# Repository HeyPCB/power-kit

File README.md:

# HeyPCB Power Kit

Six small power and charging boards, each a complete KiCad 10 project with Gerbers, BOM and a CPL fitted to JLCPCB's own footprints.

| Board | What it does | Size | DRC errors / unconnected / parity |
|---|---|---|---|
| [Dual Rail](boards/dual-rail/) | 6-15 V to 5 V / 3 A + 3.3 V / 2 A | 50 x 36 mm, 4 layers | 0 / 0 / 0 |
| [PD Trigger](boards/pd-trigger/) | USB-C PD sink, DIP-selected 5-20 V | 28 x 40 mm, 2 layers | 0 / 0 / 0 |
| [1S Boost](boards/boost-1s/) | One lithium cell to 5.1 V | 28 x 30 mm, 2 layers | 0 / 0 / 0 |
| [Power Mux](boards/power-mux/) | USB-C first, 1S cell as backup | 28 x 32 mm, 2 layers | 0 / 0 / 0 |
| [USB eFuse](boards/usb-efuse/) | 5 V inline protection | 26 x 30 mm, 2 layers | 0 / 0 / 0 |
| [USB-C Power Meter](boards/usb-c-meter/) | Inline power monitor, Qwiic | 32 x 24 mm, 2 layers | 0 / 0 / 0 |

<p align="center">     </p>

**Not fabricated, assembled or powered.** Every number in a board's README is measured by KiCad 10 on the files in its folder (`report.json`). Parts are LCSC-numbered and were in JLCPCB's stock on the date each README gives.

Each board folder holds `kicad/` (project), `fab/` (Gerbers zip, BOM, CPL, STEP, schematic PDF), `media/` (renders and a design-process video) and `board.json` (the brief it was built from).

Designed with the HeyPCB method on KiCad 10 by heypcb-kicad's headless pipeline with Freerouting 2.4.1.

## Licence

CERN-OHL-S-2.0, © 2026 heypcb.ai. See [LICENSE](LICENSE).

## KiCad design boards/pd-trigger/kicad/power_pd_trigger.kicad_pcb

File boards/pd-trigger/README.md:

# PD Trigger

A USB-C Power Delivery trigger: any PD charger in, a fixed 5, 9, 12, 15 or 20 V at 3 A out on a screw terminal, picked with a DIP switch.

| Layers | Size | Parts | Nets | Connections routed | Vias | ERC errors | DRC errors / unconnected / parity |
|---|---|---|---|---|---|---|---|
| 2 | 28 x 40 mm | 17 | 15 | 47 -> 0 open | 35 | 0 | 0 / 0 / 0 |

**Not fabricated, assembled or powered.** Every number on this page is measured by KiCad 10 on the files in this folder; the full measurements are in [`report.json`](report.json).

| | |
|---|---|
| KiCad project | [`kicad/`](kicad/) |
| Gerbers, BOM, CPL, STEP, schematic PDF | [`fab/`](fab/) |
| Renders | [top](media/top.png), [bottom](media/bottom.png) |
| Design process, every step as KiCad rendered it | [`media/design-process.mp4`](media/design-process.mp4) |

Plug a USB-C PD charger in and get one fixed voltage out, for powering a bench project, a strip of LEDs or a 12 V tool from a laptop charger. A Hynetek HUSB238 negotiates the contract and only then turns on a P-FET onto the output terminal, so nothing downstream sees a voltage it did not ask for. A 4-way DIP switch picks 5, 9, 12 or 15 V; all switches off asks for 20 V. Designed with the HeyPCB method on KiCad 10, by heypcb-kicad's headless pipeline with Freerouting 2.4.1, from the brief in `board.json`.

## Specs

- **Input:** USB-C receptacle (CC1 and CC2 to the HUSB238; D+ and D- wired for chargers that look at them).
- **Voltage select:** a 4-way DIP switch puts one resistor on VSET (HUSB238 table 6): 0 = 5 V, 6.04k = 9 V, 10k = 12 V, 14k = 15 V, nothing = 20 V. Turn on one switch at most; the positions are labelled on both faces.
- **Current request:** ISET 22.6k = 3.0 A. Not 3.25 A (ISET open), because a standard 3 A charger cannot meet 3.25 A and the HUSB238 would fall back to a lower voltage.
- **Output switch:** DMP3013SFV P-FET (-30 V, 9.5 mOhm at VGS -10 V, about 0.09 W at 3 A) driven by the HUSB238's open-drain GATE through 10k, with a 10 V zener holding VGS inside its rating at 20 V.
- **Output:** 5 mm MaiXu MX126 2-pin screw terminal, SMBJ24A TVS across it, green LED when the output is on.
- **Current paths:** VBUS and the switched output are copper zones, not tracks.
- **Board:** 28 x 40 mm, 2 layers, 1.6 mm.

## Parts

Every line carries an LCSC part number. Stock is JLCPCB's assembly stock on 2026-10-18.

| Designators | Value | LCSC | MPN | JLCPCB tier | Stock |
|---|---|---|---|---|---|
| C1 | 1uF | C15849 | CL10A105KB8NNNC | Basic | 9,261,663 |
| C2 | 1uF | C28323 | CL21B105KBFNNNE | Basic | 2,337,702 |
| D1 | BZT52C10 | C173431 | BZT52C10 | Extended | 277,380 |
| D2 | SMBJ24A | C123819 | SMBJ24A | Extended | 59,843 |
| D3 | Green (OUT) | C12624 | KT-0603G | Extended | 500,718 |
| J1 | USB-C PD IN | C165948 | TYPE-C-31-M-12 | Extended | 362,231 |
| J2 | OUT | C5188434 | MX126-5.0-02P-GN01-Cu-S-A | Extended | 35,962 |
| Q1 | DMP3013SFV | C264098 | DMP3013SFV-7 | Extended | 3,984 |
| R1 | 6.04k | C25977 | 0603WAF6041T5E | Extended | 135,034 |
| R2,R5,R7 | 10k | C25804 | 0603WAF1002T5E | Basic | 39,990,901 |
| R3 | 14k | C22803 | 0603WAF1402T5E | Extended | 11,051 |
| R4 | 22.6k | C2999509 | FRC0603F2262TS | Extended | 92,673 |
| R6 | 100k | C25803 | 0603WAF1003T5E | Basic | 19,336,314 |
| SW1 | VSET 5/9/12/15 | C6331176 | 2.54-4P TPGT | Extended | 45,129 |
| U1 | HUSB238_002DD | C7471904 | HUSB238_002DD | Extended | 13,737 |

## Ordering

- PCB: upload `fab/power_pd_trigger_gerbers.zip`, 2 layers, 28 x 40 mm, 1.6 mm.
- Assembly: `fab/power_pd_trigger_bom.csv` and `fab/power_pd_trigger_cpl_jlc.csv`, top side.
- The CPL is fitted to each part's own JLCPCB footprint, pad by pad, and re-checked by laying each footprint where its row says: 17 of 17 rows fitted, worst pin-to-pad offset 0.21 mm.

## Notes

- The 3 A rating is the request the board makes; whether a charger gives 3 A at the chosen voltage is the charger's PDO list. Nothing here is measured at load: the board has not been built.
- The DMP3013SFV (C264098) had 3,984 in JLCPCB's stock when this was packaged, the lowest of the parts list. Check it before ordering.
- SDA and SCL are not connected; the HUSB238's I2C mode is not used.
- The USB-C receptacle (HRO TYPE-C-31-M-12) renders as a plain box: KiCad's library footprint names a 3D model that KiCad does not ship. The footprint and its pads are KiCad's own and are fitted to JLCPCB's land.

## How it was made

Designed with the HeyPCB method on KiCad 10, by heypcb-kicad's headless pipeline with Freerouting 2.4.1, from the brief in [`board.json`](board.json).

## Licence

CERN-OHL-S-2.0, © 2026 heypcb.ai. See the collection's LICENSE.

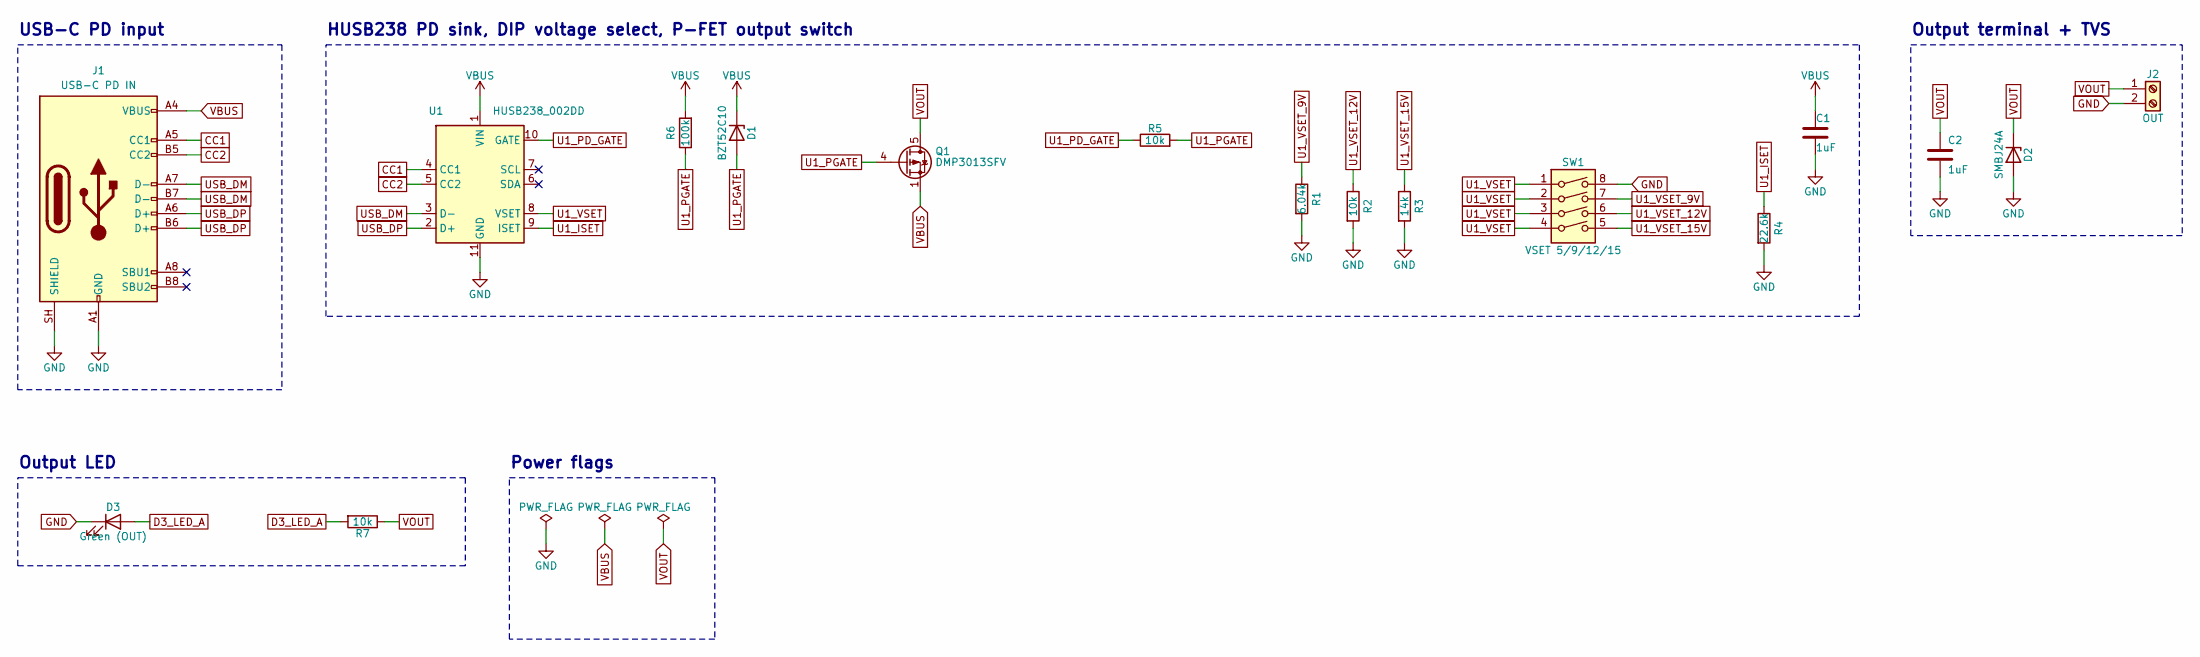
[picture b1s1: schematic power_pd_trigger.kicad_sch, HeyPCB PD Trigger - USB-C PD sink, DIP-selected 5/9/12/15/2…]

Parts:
C1: 1uF; C_0603_1608Metric; MPN CL10A105KB8NNNC; LCSC C15849
C2: 1uF; C_0805_2012Metric; MPN CL21B105KBFNNNE; LCSC C28323
D1: BZT52C10; D_SOD-123; MPN BZT52C10; LCSC C173431
D2: SMBJ24A; D_SMB; MPN SMBJ24A; LCSC C123819
D3: Green (OUT); LED_0603_1608Metric; MPN KT-0603G; LCSC C12624
J1: USB-C PD IN; USB_C_Receptacle_HRO_TYPE-C-31-M-12; MPN TYPE-C-31-M-12; LCSC C165948
J2: OUT; TerminalBlock_MaiXu_MX126-5.0-02P_1x02_P5.00mm; MPN MX126-5.0-02P-GN01-Cu-S-A; LCSC C5188434
Q1: DMP3013SFV; Diodes_PowerDI3333-8; MPN DMP3013SFV-7; LCSC C264098
R1: 6.04k; R_0603_1608Metric; MPN 0603WAF6041T5E; LCSC C25977
R2, R5, R7: 10k; R_0603_1608Metric; MPN 0603WAF1002T5E; LCSC C25804
R3: 14k; R_0603_1608Metric; MPN 0603WAF1402T5E; LCSC C22803
R4: 22.6k; R_0603_1608Metric; MPN FRC0603F2262TS; LCSC C2999509
R6: 100k; R_0603_1608Metric; MPN 0603WAF1003T5E; LCSC C25803
SW1: VSET 5/9/12/15; SW_DIP_SPSTx04_Slide_Omron_A6S-410x_W8.9mm_P2.54mm; MPN 2.54-4P TPGT; LCSC C6331176
U1: HUSB238_002DD; WDFN-10-1EP_3x3mm_P0.5mm_EP1.8x2.5mm; MPN HUSB238_002DD; LCSC C7471904

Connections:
CC1: J1.A5 (CC1), U1.4 (CC1)
CC2: J1.B5 (CC2), U1.5 (CC2)
D3_LED_A: D3.2 (A), R7.2
GND: C1.2, C2.2, D2.2 (A), D3.1 (K), J1.A1 (GND), J1.A12 (GND), J1.B1 (GND), J1.B12 (GND), J1.SH (SHIELD), J2.2, R1.2, R2.2, R3.2, R4.2, SW1.8, U1.11 (GND)
U1_ISET: R4.1, U1.9 (ISET)
U1_PD_GATE: R5.1, U1.10 (GATE)
U1_PGATE: D1.2 (A), Q1.4 (G), R5.2, R6.1
U1_VSET: SW1.1, SW1.2, SW1.3, SW1.4, U1.8 (VSET)
U1_VSET_9V: R1.1, SW1.7
U1_VSET_12V: R2.1, SW1.6
U1_VSET_15V: R3.1, SW1.5
USB_DM: J1.A7 (D-), J1.B7 (D-), U1.3 (D-)
USB_DP: J1.A6 (D+), J1.B6 (D+), U1.2 (D+)
VBUS: C1.1, D1.1 (K), J1.A4 (VBUS), J1.A9 (VBUS), J1.B4 (VBUS), J1.B9 (VBUS), Q1.1 (S), Q1.2 (S), Q1.3 (S), R6.2, U1.1 (VIN)
VOUT: C2.1, D2.1 (K), J2.1, Q1.5 (D), R7.1

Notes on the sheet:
USB-C PD input
HUSB238 PD sink, DIP voltage select, P-FET output switch
Output terminal + TVS
Output LED
Power flags

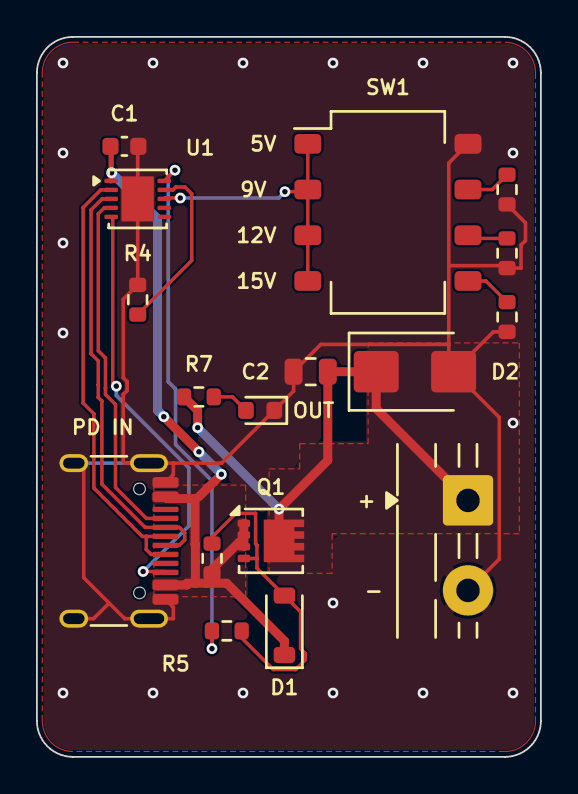
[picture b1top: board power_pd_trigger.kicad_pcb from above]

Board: 2 copper layers, 28.0 x 40.0 mm, 17 parts (0 on the bottom side), 15 nets.

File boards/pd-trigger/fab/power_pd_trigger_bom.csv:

"Reference","Value","Footprint","MPN","LCSC","Qty"
"C1","1uF","Capacitor_SMD:C_0603_1608Metric","CL10A105KB8NNNC","C15849","1"
"C2","1uF","Capacitor_SMD:C_0805_2012Metric","CL21B105KBFNNNE","C28323","1"
"D1","BZT52C10","Diode_SMD:D_SOD-123","BZT52C10","C173431","1"
"D2","SMBJ24A","Diode_SMD:D_SMB","SMBJ24A","C123819","1"
"D3","Green (OUT)","LED_SMD:LED_0603_1608Metric","KT-0603G","C12624","1"
"J1","USB-C PD IN","Connector_USB:USB_C_Receptacle_HRO_TYPE-C-31-M-12","TYPE-C-31-M-12","C165948","1"
"J2","OUT","TerminalBlock:TerminalBlock_MaiXu_MX126-5.0-02P_1x02_P5.00mm","MX126-5.0-02P-GN01-Cu-S-A","C5188434","1"
"Q1","DMP3013SFV","Package_SON:Diodes_PowerDI3333-8","DMP3013SFV-7","C264098","1"
"R1","6.04k","Resistor_SMD:R_0603_1608Metric","0603WAF6041T5E","C25977","1"
"R2,R5,R7","10k","Resistor_SMD:R_0603_1608Metric","0603WAF1002T5E","C25804","3"
"R3","14k","Resistor_SMD:R_0603_1608Metric","0603WAF1402T5E","C22803","1"
"R4","22.6k","Resistor_SMD:R_0603_1608Metric","FRC0603F2262TS","C2999509","1"
"R6","100k","Resistor_SMD:R_0603_1608Metric","0603WAF1003T5E","C25803","1"
"SW1","VSET 5/9/12/15","Button_Switch_SMD:SW_DIP_SPSTx04_Slide_Omron_A6S-410x_W8.9mm_P2.54mm","2.54-4P TPGT","C6331176","1"
"U1","HUSB238_002DD","Package_DFN_QFN:WDFN-10-1EP_3x3mm_P0.5mm_EP1.8x2.5mm","HUSB238_002DD","C7471904","1"

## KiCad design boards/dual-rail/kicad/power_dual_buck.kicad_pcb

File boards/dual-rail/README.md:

# Dual Rail

A dual-rail buck module: 6-15 V in, 5 V / 3 A and 3.3 V / 2 A out, reverse-polarity protected.

| Layers | Size | Parts | Nets | Connections routed | Vias | ERC errors | DRC errors / unconnected / parity |
|---|---|---|---|---|---|---|---|
| 4 | 50 x 36 mm | 34 | 14 | 57 -> 0 open | 70 | 0 | 0 / 0 / 0 |

**Not fabricated, assembled or powered.** Every number on this page is measured by KiCad 10 on the files in this folder; the full measurements are in [`report.json`](report.json).

| | |
|---|---|
| KiCad project | [`kicad/`](kicad/) |
| Gerbers, BOM, CPL, STEP, schematic PDF | [`fab/`](fab/) |
| Renders | [top](media/top.png), [bottom](media/bottom.png) |
| Design process, every step as KiCad rendered it | [`media/design-process.mp4`](media/design-process.mp4) |

A small power module for the bench and for projects that need both 5 V and 3.3 V from one 6-15 V supply (a 12 V adapter, a 3S pack). A TPS563201 synchronous buck makes 5 V and an AP63203 makes 3.3 V, both straight from the protected input, so neither rail's load heats the other's regulator. The input has a reverse-polarity P-FET and a TVS, every rail has an LED, and VIN, 5V, 3V3 and GND come out on a 2.54 mm header. Designed with the HeyPCB method on KiCad 10 (10.0.6), by heypcb-kicad's headless pipeline with Freerouting 2.4.1, from the brief in `board.json`.

## Specs

- **Input:** 6-15 V DC on a 5 mm MaiXu MX126 screw terminal, marked + and -. The input range stops at 15 V because the TPS563201 is rated to 17 V input (TI SLVSD90B).
- **Reverse polarity:** AO3401A P-FET in the + lead (drain on the terminal, source on the board). A BZT52C10 zener and a 100k resistor hold its gate-source voltage at about -10 V, inside its +-12 V rating, across the whole input range.
- **Transients:** SMAJ15A TVS on the protected input (15 V stand-off, 24.4 V clamp at 16.4 A). It is for transients, not for a sustained over-voltage. 2 x 22 uF / 25 V X5R input bulk.
- **5 V rail:** TPS563201 synchronous buck (TI, 3 A, 580 kHz), 4.7 uH Sunlord SWPA6045S inductor, 3 x 22 uF output. Feedback 82k / 15k: VFB 0.768 V gives 4.96 V.
- **3.3 V rail:** AP63203 fixed 3.3 V synchronous buck (Diodes, 2 A, 1.1 MHz), 4.7 uH Sunlord SWPA4030S inductor, 2 x 22 uF output.
- **Current paths:** the raw input, the protected input, both switch nodes, 5V and 3V3 are copper zones on F.Cu, not tracks. The input zones at each converter are stitched to an In2 VIN plane, and In1 is a solid GND plane.
- **Outputs:** VIN, 5V, 3V3 and GND on a 1x4 2.54 mm header, labelled on both faces; a green LED on each rail.
- **Board:** 50 x 36 mm, 4 layers (F.Cu / In1 GND / In2 VIN + routing / B.Cu), 1.6 mm, four M3 holes at the corners.

## Parts

Every line carries an LCSC part number. Stock is JLCPCB's assembly stock on 2026-10-18.

| Designators | Value | LCSC | MPN | JLCPCB tier | Stock |
|---|---|---|---|---|---|
| C1,C2 | 22uF | C12891 | CL31A226KAHNNNE | Basic | 490,725 |
| C3,C4,C7,C8,C9,C12,C13 | 22uF | C45783 | CL21A226MAQNNNE | Basic | 3,755,166 |
| C5,C6,C11 | 100nF | C14663 | CC0603KRX7R9BB104 | Basic | 31,787,100 |
| C10 | 10uF | C13585 | CL31A106KBHNNNE | Basic | 2,283,157 |
| D1 | BZT52C10 | C173431 | BZT52C10 | Extended | 277,380 |
| D2 | SMAJ15A | C908769 | SMAJ15A | Extended | 112,547 |
| D3 | Green (5V) | C12624 | KT-0603G | Extended | 500,718 |
| D4 | Green (3V3) | C12624 | KT-0603G | Extended | 500,718 |
| J1 | VIN 6-15V | C5188434 | MX126-5.0-02P-GN01-Cu-S-A | Extended | 35,962 |
| J2 | OUT | C2691448 | PZ254V-11-04P | Extended | 887,860 |
| L1 | 4.7uH | C78804 | SWPA6045S4R7MT | Extended | 30,574 |
| L2 | 4.7uH | C57269 | SWPA4030S4R7MT | Extended | 19,258 |
| Q1 | AO3401A | C15127 | AO3401A | Basic | 696,636 |
| R1,R4 | 100k | C25803 | 0603WAF1003T5E | Basic | 19,342,480 |
| R2 | 82k | C23254 | 0603WAF8202T5E | Basic | 1,210,269 |
| R3 | 15k | C22809 | 0603WAF1502T5E | Basic | 4,101,125 |
| R5 | 2.2k | C4190 | 0603WAF2201T5E | Basic | 6,541,747 |
| R6 | 1k | C21190 | 0603WAF1001T5E | Basic | 23,229,534 |
| U1 | TPS563201 | C116592 | TPS563201DDCR | Extended | 114,139 |
| U2 | AP63203WU-7 | C780769 | AP63203WU-7 | Extended | 3,515 |

## Ordering

- PCB: upload `fab/power_dual_buck_gerbers.zip`, 4 layers, 50 x 36 mm, 1.6 mm.
- Assembly: `fab/power_dual_buck_bom.csv` and `fab/power_dual_buck_cpl_jlc.csv`, top side.
- The CPL is fitted to each part's own JLCPCB footprint, pad by pad, and re-checked by laying each footprint where its row says: 28 of 30 rows fitted, worst pin-to-pad offset 0.28 mm.
- Not fitted (no JLCPCB footprint to fit to), rotation from KiCad's: L1, L2. Check these in JLCPCB's placement preview.

## Notes

- The output ratings (3 A, 2 A) are the converters' datasheet ratings. Nothing here measures temperature or ripple at load: the board has not been built.
- The AP63203WU-7 (C780769) has one LCSC listing; 3,515 in stock when this was packaged. The same part is on PD Brick, Spinner and Ice Core.
- L1 and L2 (Sunlord SWPA inductors) are not in EasyEDA's footprint library, so their CPL rotation is KiCad's and was not fitted. Both are symmetric two-pad parts with their pads along x in KiCad. Check them in JLCPCB's placement preview.

## How it was made

Designed with the HeyPCB method on KiCad 10, by heypcb-kicad's headless pipeline with Freerouting 2.4.1, from the brief in [`board.json`](board.json).

## Licence

CERN-OHL-S-2.0, © 2026 heypcb.ai. See the collection's LICENSE.

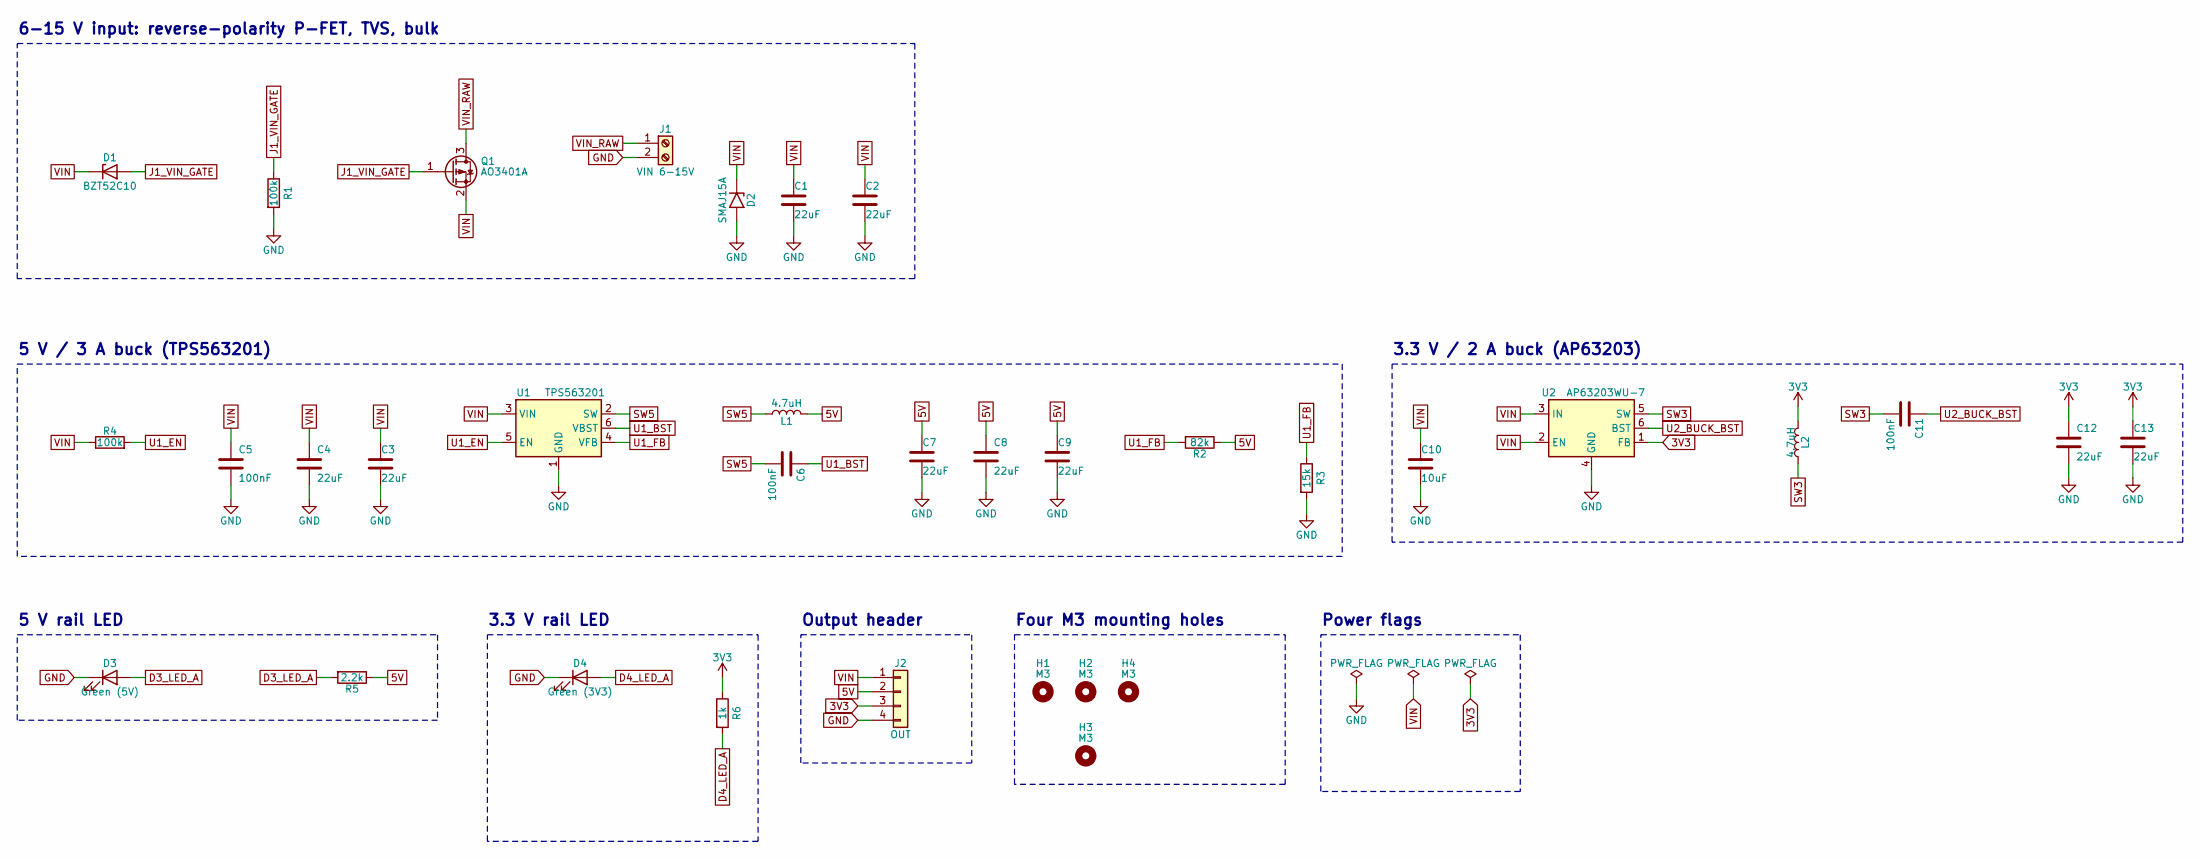
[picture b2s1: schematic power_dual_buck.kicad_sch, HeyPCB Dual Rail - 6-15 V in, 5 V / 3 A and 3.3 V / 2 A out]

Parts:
C1, C2: 22uF; C_1206_3216Metric; MPN CL31A226KAHNNNE; LCSC C12891
C3, C4, C7, C8, C9, C12, C13: 22uF; C_0805_2012Metric; MPN CL21A226MAQNNNE; LCSC C45783
C5, C6, C11: 100nF; C_0603_1608Metric; MPN CC0603KRX7R9BB104; LCSC C14663
C10: 10uF; C_1206_3216Metric; MPN CL31A106KBHNNNE; LCSC C13585
D1: BZT52C10; D_SOD-123; MPN BZT52C10; LCSC C173431
D2: SMAJ15A; D_SMA; MPN SMAJ15A; LCSC C908769
D3: Green (5V); LED_0603_1608Metric; MPN KT-0603G; LCSC C12624
D4: Green (3V3); LED_0603_1608Metric; MPN KT-0603G; LCSC C12624
H1, H2, H3, H4: M3; MountingHole_3.2mm_M3
J1: VIN 6-15V; TerminalBlock_MaiXu_MX126-5.0-02P_1x02_P5.00mm; MPN MX126-5.0-02P-GN01-Cu-S-A; LCSC C5188434
J2: OUT; PinHeader_1x04_P2.54mm_Vertical; MPN PZ254V-11-04P; LCSC C2691448
L1: 4.7uH; L_Sunlord_SWPA6045S; MPN SWPA6045S4R7MT; LCSC C78804
L2: 4.7uH; L_Sunlord_SWPA4030S; MPN SWPA4030S4R7MT; LCSC C57269
Q1: AO3401A; SOT-23; MPN AO3401A; LCSC C15127
R1, R4: 100k; R_0603_1608Metric; MPN 0603WAF1003T5E; LCSC C25803
R2: 82k; R_0603_1608Metric; MPN 0603WAF8202T5E; LCSC C23254
R3: 15k; R_0603_1608Metric; MPN 0603WAF1502T5E; LCSC C22809
R5: 2.2k; R_0603_1608Metric; MPN 0603WAF2201T5E; LCSC C4190
R6: 1k; R_0603_1608Metric; MPN 0603WAF1001T5E; LCSC C21190
U1: TPS563201; SOT-23-6; MPN TPS563201DDCR; LCSC C116592
U2: AP63203WU-7; TSOT-23-6; MPN AP63203WU-7; LCSC C780769

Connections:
3V3: C12.1, C13.1, J2.3, L2.2, R6.1, U2.1 (FB)
5V: C7.1, C8.1, C9.1, J2.2, L1.2, R2.1, R5.1
D3_LED_A: D3.2 (A), R5.2
D4_LED_A: D4.2 (A), R6.2
GND: C1.2, C2.2, C3.2, C4.2, C5.2, C7.2, C8.2, C9.2, C10.2, C12.2, C13.2, D2.2 (A2), D3.1 (K), D4.1 (K), J1.2, J2.4, R1.2, R3.2, U1.1 (GND), U2.4 (GND)
J1_VIN_GATE: D1.2 (A), Q1.1 (G), R1.1
SW3: C11.2, L2.1, U2.5 (SW)
SW5: C6.2, L1.1, U1.2 (SW)
U1_BST: C6.1, U1.6 (VBST)
U1_EN: R4.2, U1.5 (EN)
U1_FB: R2.2, R3.1, U1.4 (VFB)
U2_BUCK_BST: C11.1, U2.6 (BST)
VIN: C1.1, C2.1, C3.1, C4.1, C5.1, C10.1, D1.1 (K), D2.1 (A1), J2.1, Q1.2 (S), R4.1, U1.3 (VIN), U2.2 (EN), U2.3 (IN)
VIN_RAW: J1.1, Q1.3 (D)

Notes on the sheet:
6-15 V input: reverse-polarity P-FET, TVS, bulk
5 V / 3 A buck (TPS563201)
3.3 V / 2 A buck (AP63203)
5 V rail LED
3.3 V rail LED
Output header
Four M3 mounting holes
Power flags

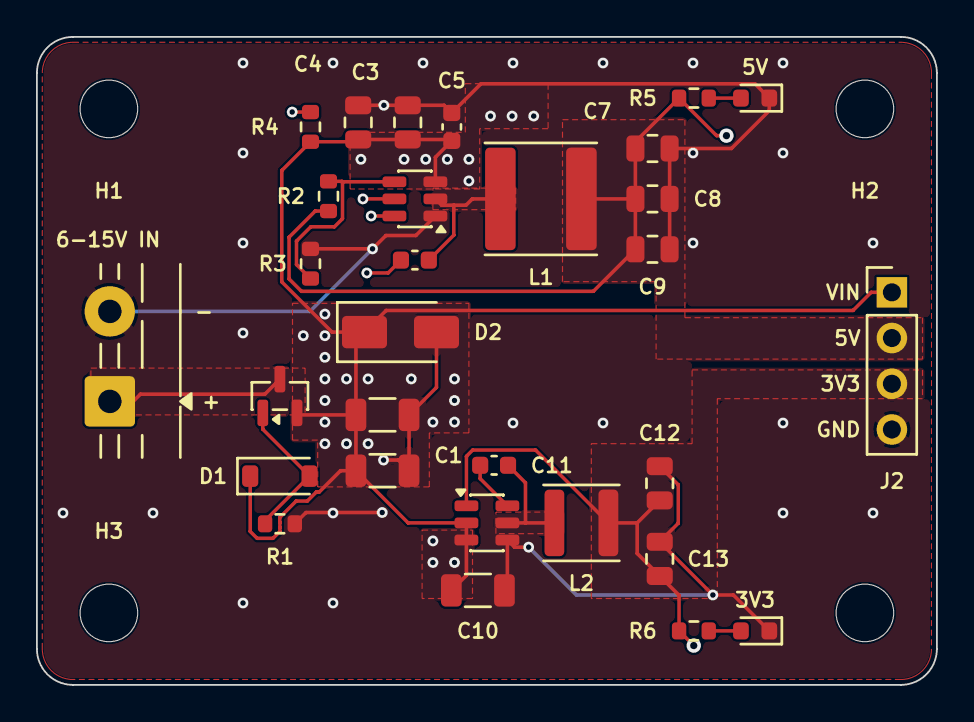
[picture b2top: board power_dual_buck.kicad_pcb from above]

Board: 4 copper layers, 50.0 x 36.0 mm, 34 parts (0 on the bottom side), 14 nets.

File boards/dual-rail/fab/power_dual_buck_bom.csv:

"Reference","Value","Footprint","MPN","LCSC","Qty"
"C1,C2","22uF","Capacitor_SMD:C_1206_3216Metric","CL31A226KAHNNNE","C12891","2"
"C3,C4,C7,C8,C9,C12,C13","22uF","Capacitor_SMD:C_0805_2012Metric","CL21A226MAQNNNE","C45783","7"
"C5,C6,C11","100nF","Capacitor_SMD:C_0603_1608Metric","CC0603KRX7R9BB104","C14663","3"
"C10","10uF","Capacitor_SMD:C_1206_3216Metric","CL31A106KBHNNNE","C13585","1"
"D1","BZT52C10","Diode_SMD:D_SOD-123","BZT52C10","C173431","1"
"D2","SMAJ15A","Diode_SMD:D_SMA","SMAJ15A","C908769","1"
"D3","Green (5V)","LED_SMD:LED_0603_1608Metric","KT-0603G","C12624","1"
"D4","Green (3V3)","LED_SMD:LED_0603_1608Metric","KT-0603G","C12624","1"
"J1","VIN 6-15V","TerminalBlock:TerminalBlock_MaiXu_MX126-5.0-02P_1x02_P5.00mm","MX126-5.0-02P-GN01-Cu-S-A","C5188434","1"
"J2","OUT","Connector_PinHeader_2.54mm:PinHeader_1x04_P2.54mm_Vertical","PZ254V-11-04P","C2691448","1"
"L1","4.7uH","Inductor_SMD:L_Sunlord_SWPA6045S","SWPA6045S4R7MT","C78804","1"
"L2","4.7uH","Inductor_SMD:L_Sunlord_SWPA4030S","SWPA4030S4R7MT","C57269","1"
"Q1","AO3401A","Package_TO_SOT_SMD:SOT-23","AO3401A","C15127","1"
"R1,R4","100k","Resistor_SMD:R_0603_1608Metric","0603WAF1003T5E","C25803","2"
"R2","82k","Resistor_SMD:R_0603_1608Metric","0603WAF8202T5E","C23254","1"
"R3","15k","Resistor_SMD:R_0603_1608Metric","0603WAF1502T5E","C22809","1"
"R5","2.2k","Resistor_SMD:R_0603_1608Metric","0603WAF2201T5E","C4190","1"
"R6","1k","Resistor_SMD:R_0603_1608Metric","0603WAF1001T5E","C21190","1"
"U1","TPS563201","Package_TO_SOT_SMD:SOT-23-6","TPS563201DDCR","C116592","1"
"U2","AP63203WU-7","Package_TO_SOT_SMD:TSOT-23-6","AP63203WU-7","C780769","1"

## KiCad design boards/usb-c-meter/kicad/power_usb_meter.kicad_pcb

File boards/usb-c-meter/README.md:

# USB-C Power Meter

Put it in a USB-C cable run and read volts, amps and watts over Qwiic: an INA226 on a 10 mOhm shunt in VBUS, with CC and USB 2.0 passed straight through.

| Layers | Size | Parts | Nets | Connections routed | Vias | ERC errors | DRC errors / unconnected / parity |
|---|---|---|---|---|---|---|---|
| 2 | 32 x 24 mm | 8 | 10 | 41 -> 0 open | 35 | 0 | 0 / 0 / 0 |

**Not fabricated, assembled or powered.** Every number on this page is measured by KiCad 10 on the files in this folder; the full measurements are in [`report.json`](report.json).

| | |
|---|---|
| KiCad project | [`kicad/`](kicad/) |
| Gerbers, BOM, CPL, STEP, schematic PDF | [`fab/`](fab/) |
| Renders | [top](media/top.png), [bottom](media/bottom.png) |
| Design process, every step as KiCad rendered it | [`media/design-process.mp4`](media/design-process.mp4) |

A small inline meter for logging what a USB-C device actually draws: plug the charger into IN and the device into OUT, connect the Qwiic port to a microcontroller, and read the bus voltage, current and power from an INA226 at I2C address 0x40. CC1 and CC2 run straight through, so a USB PD charger and sink still negotiate with each other, and D+ / D- pass through for USB 2.0. Designed with the HeyPCB method on KiCad 10, by heypcb-kicad's headless pipeline with Freerouting 2.4.1, from the brief in `board.json`.

## Specs

- **Pass-through:** two HRO TYPE-C-31-M-12 receptacles (USB 2.0, 16 pins); VBUS through the shunt, CC1, CC2, D+ and D- wired straight across. No resistors on CC: the board is not a source or a sink, the devices on either side are.
- **Measurement:** INA226 (TI), high side, shunt 10 mOhm 1 % 1 W (FMF06FTHR010-LH). Full scale 81.92 mV / 10 mOhm = 8.19 A, one LSB 0.25 mA; bus voltage 0-36 V at 1.25 mV per LSB, taken on the load side so the power is what the device receives. Covers 5-20 V USB PD.
- **Interface:** Qwiic / STEMMA QT (JST SH 4-pin): GND, 3.3 V, SDA, SCL. The INA226 runs from the Qwiic 3.3 V; 4.7k pull-ups on SDA and SCL. Address 0x40 (A0 = A1 = GND). Alert is not connected.
- **Current paths:** VBUS on each side of the shunt is a zone on both layers, stitched; tracks are kept off B.Cu between the receptacles so the bottom-layer VBUS planes stay whole.
- **Board:** 32 x 24 mm, 2 layers, 1.6 mm.

## Parts

Every line carries an LCSC part number. Stock is JLCPCB's assembly stock on 2026-10-18.

| Designators | Value | LCSC | MPN | JLCPCB tier | Stock |
|---|---|---|---|---|---|
| C1 | 100nF | C28233 | CL21B104KCFNNNE | Basic | 1,356,236 |
| J1 | USB-C IN | C165948 | TYPE-C-31-M-12 | Extended | 362,213 |
| J2 | USB-C OUT | C165948 | TYPE-C-31-M-12 | Extended | 362,213 |
| J3 | QWIIC | C160404 | SM04B-SRSS-TB(LF)(SN) | Extended | 60,043 |
| R1 | 10m | C105362 | FMF06FTHR010-LH | Extended | 145,294 |
| R2,R3 | 4.7k | C23162 | 0603WAF4701T5E | Basic | 18,626,473 |
| U1 | INA226 | C49851 | INA226AIDGSR | Extended | 39,617 |

## Ordering

- PCB: upload `fab/power_usb_meter_gerbers.zip`, 2 layers, 32 x 24 mm, 1.6 mm.
- Assembly: `fab/power_usb_meter_bom.csv` and `fab/power_usb_meter_cpl_jlc.csv`, top side.
- The CPL is fitted to each part's own JLCPCB footprint, pad by pad, and re-checked by laying each footprint where its row says: 8 of 8 rows fitted, worst pin-to-pad offset 0.07 mm.

## Notes

- Made for 3 A. On the IN receptacle the zone joins the lower VBUS pad (contacts A9 / B4) to the shunt directly; the upper pad (A4 / B9) reaches it through a 0.2 mm track about 3 mm long, because the CC and USB 2.0 tracks leave the receptacle between the two pads. The OUT side's zone joins both pads.
- The silkscreen marks OUT beside the right receptacle; the IN word found no free spot beside the left one, which is the side with the Qwiic label above it. The supply goes in on the left.
- USB 2.0 data crosses the board on plain 0.2 mm tracks, not an impedance-controlled pair: full speed will be fine; high speed is not verified.
- The board draws nothing from VBUS: without a Qwiic host it is a passive pass-through.
- The USB-C receptacles render as plain boxes: KiCad's library footprint names a 3D model that KiCad does not ship. The footprint and its pads are KiCad's own and are fitted to JLCPCB's land.
- Not built or measured: accuracy, the 3 A rating and USB 2.0 signal quality are unverified.

## How it was made

Designed with the HeyPCB method on KiCad 10, by heypcb-kicad's headless pipeline with Freerouting 2.4.1, from the brief in [`board.json`](board.json).

## Licence

CERN-OHL-S-2.0, © 2026 heypcb.ai. See the collection's LICENSE.

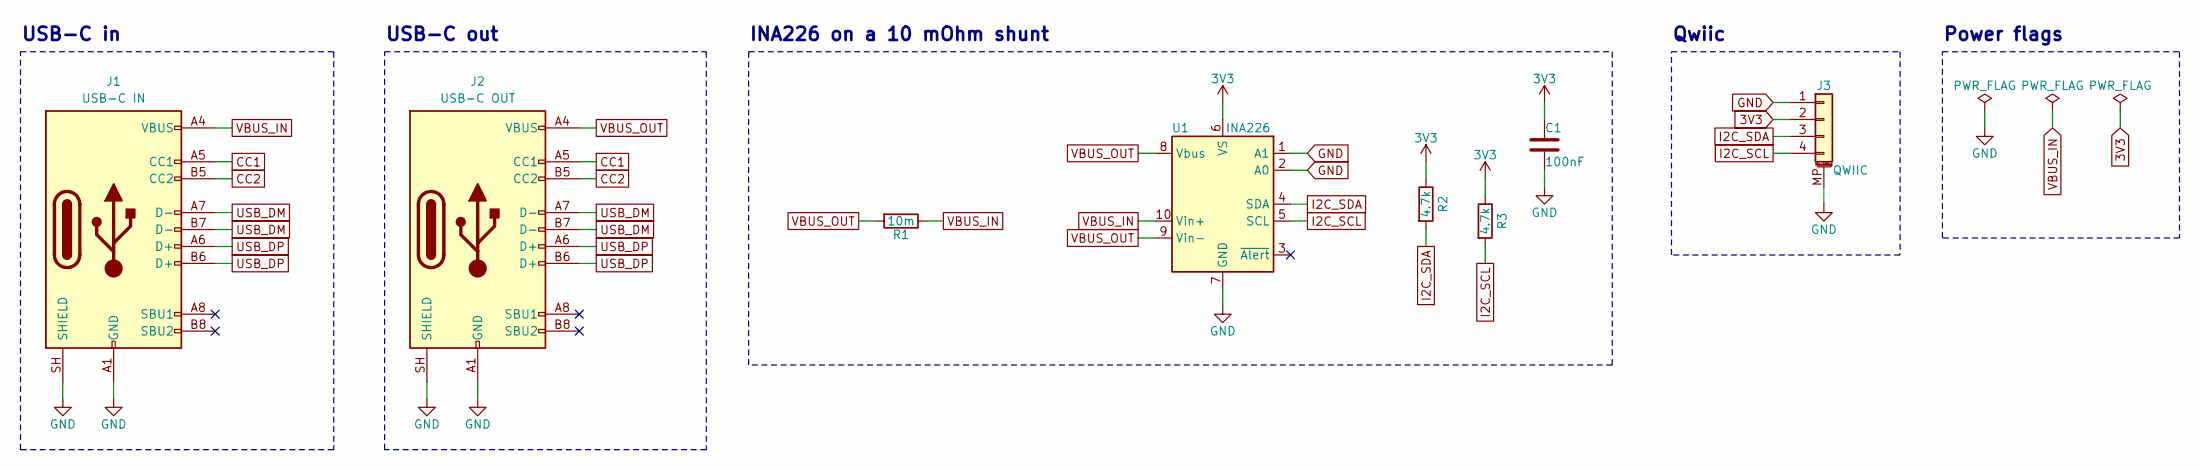
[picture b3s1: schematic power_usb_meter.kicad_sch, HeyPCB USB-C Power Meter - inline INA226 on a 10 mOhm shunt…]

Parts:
C1: 100nF; C_0805_2012Metric; MPN CL21B104KCFNNNE; LCSC C28233
J1: USB-C IN; USB_C_Receptacle_HRO_TYPE-C-31-M-12; MPN TYPE-C-31-M-12; LCSC C165948
J2: USB-C OUT; USB_C_Receptacle_HRO_TYPE-C-31-M-12; MPN TYPE-C-31-M-12; LCSC C165948
J3: QWIIC; JST_SH_SM04B-SRSS-TB_1x04-1MP_P1.00mm_Horizontal; MPN SM04B-SRSS-TB(LF)(SN); LCSC C160404
R1: 10m; R_1206_3216Metric; MPN FMF06FTHR010-LH; LCSC C105362
R2, R3: 4.7k; R_0603_1608Metric; MPN 0603WAF4701T5E; LCSC C23162
U1: INA226; TSSOP-10_3x3mm_P0.5mm; MPN INA226AIDGSR; LCSC C49851

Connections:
3V3: C1.1, J3.2, R2.1, R3.1, U1.6 (VS)
CC1: J1.A5 (CC1), J2.A5 (CC1)
CC2: J1.B5 (CC2), J2.B5 (CC2)
GND: C1.2, J1.A1 (GND), J1.A12 (GND), J1.B1 (GND), J1.B12 (GND), J1.SH (SHIELD), J2.A1 (GND), J2.A12 (GND), J2.B1 (GND), J2.B12 (GND), J2.SH (SHIELD), J3.1, J3.MP (MountPin), U1.1 (A1), U1.2 (A0), U1.7 (GND)
I2C_SCL: J3.4, R3.2, U1.5 (SCL)
I2C_SDA: J3.3, R2.2, U1.4 (SDA)
USB_DM: J1.A7 (D-), J1.B7 (D-), J2.A7 (D-), J2.B7 (D-)
USB_DP: J1.A6 (D+), J1.B6 (D+), J2.A6 (D+), J2.B6 (D+)
VBUS_IN: J1.A4 (VBUS), J1.A9 (VBUS), J1.B4 (VBUS), J1.B9 (VBUS), R1.1, U1.10 (Vin+)
VBUS_OUT: J2.A4 (VBUS), J2.A9 (VBUS), J2.B4 (VBUS), J2.B9 (VBUS), R1.2, U1.8 (Vbus), U1.9 (Vin-)

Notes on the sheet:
USB-C in
USB-C out
INA226 on a 10 mOhm shunt
Qwiic
Power flags

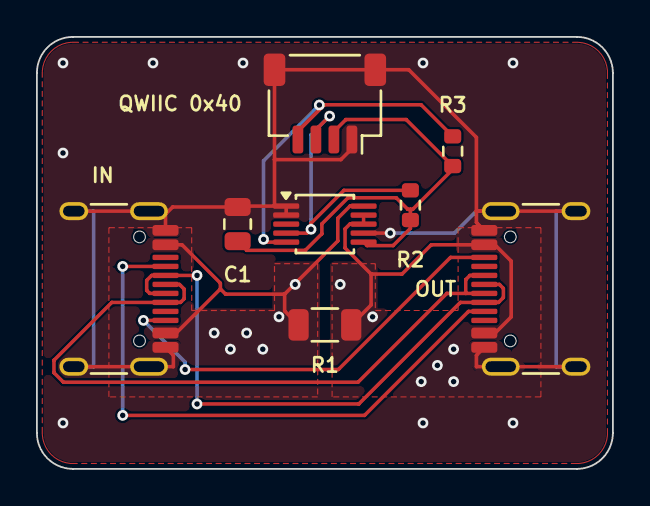
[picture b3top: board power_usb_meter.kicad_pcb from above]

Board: 2 copper layers, 32.0 x 24.0 mm, 8 parts (0 on the bottom side), 10 nets.

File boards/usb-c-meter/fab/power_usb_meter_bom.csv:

"Reference","Value","Footprint","MPN","LCSC","Qty"
"C1","100nF","Capacitor_SMD:C_0805_2012Metric","CL21B104KCFNNNE","C28233","1"
"J1","USB-C IN","Connector_USB:USB_C_Receptacle_HRO_TYPE-C-31-M-12","TYPE-C-31-M-12","C165948","1"
"J2","USB-C OUT","Connector_USB:USB_C_Receptacle_HRO_TYPE-C-31-M-12","TYPE-C-31-M-12","C165948","1"
"J3","QWIIC","Connector_JST:JST_SH_SM04B-SRSS-TB_1x04-1MP_P1.00mm_Horizontal","SM04B-SRSS-TB(LF)(SN)","C160404","1"
"R1","10m","Resistor_SMD:R_1206_3216Metric","FMF06FTHR010-LH","C105362","1"
"R2,R3","4.7k","Resistor_SMD:R_0603_1608Metric","0603WAF4701T5E","C23162","2"
"U1","INA226","Package_SO:TSSOP-10_3x3mm_P0.5mm","INA226AIDGSR","C49851","1"

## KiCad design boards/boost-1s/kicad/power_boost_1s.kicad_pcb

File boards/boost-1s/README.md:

# 1S Boost

One lithium cell in, 5.1 V out: an MT3608 boost with a JST PH input and a 2.54 mm header.

| Layers | Size | Parts | Nets | Connections routed | Vias | ERC errors | DRC errors / unconnected / parity |
|---|---|---|---|---|---|---|---|
| 2 | 28 x 30 mm | 13 | 7 | 24 -> 0 open | 24 | 0 | 0 / 0 / 0 |

**Not fabricated, assembled or powered.** Every number on this page is measured by KiCad 10 on the files in this folder; the full measurements are in [`report.json`](report.json).

| | |
|---|---|
| KiCad project | [`kicad/`](kicad/) |
| Gerbers, BOM, CPL, STEP, schematic PDF | [`fab/`](fab/) |
| Renders | [top](media/top.png), [bottom](media/bottom.png) |
| Design process, every step as KiCad rendered it | [`media/design-process.mp4`](media/design-process.mp4) |

The small board between a single Li-ion or LiPo cell and anything that wants 5 V: an Arduino, a strip of addressable LEDs, a USB gadget. The cell plugs into a JST PH connector on the left; an MT3608 boosts its 3.0-4.2 V to 5.1 V; 5V, GND, EN and the raw cell voltage come out on a 2.54 mm header on the right, labelled on both faces. Designed with the HeyPCB method on KiCad 10, by heypcb-kicad's headless pipeline with Freerouting 2.4.1, from the brief in `board.json`.

## Specs

- **Input:** one Li-ion / LiPo cell (3.0-4.2 V) on a JST S2B-PH-K side-entry connector, + and - marked beside its pads. The MT3608 runs from 2 V.
- **Converter:** MT3608 asynchronous boost (1.2 MHz, 4 A switch-current limit), 22 uH FNR4030S inductor, SS34 3 A Schottky, 22 uF in and 2 x 22 uF out (25 V X5R 1206).
- **Output:** 0.6 V x (1 + 15k / 2k) = 5.10 V. The design target is 1 A from a cell above 3.3 V; that is a datasheet-and-arithmetic figure, not a measurement.
- **EN:** pulled up to the cell through 100k, so the converter runs by default; pull EN to GND on the header to stop it.
- **Header:** 5V, GND, EN, BAT on 2.54 mm pitch, labelled on both faces; a green LED on 5V.
- **Board:** 28 x 30 mm, 2 layers, 1.6 mm; the cell, switch and output paths routed at 0.8 mm.

## Parts

Every line carries an LCSC part number. Stock is JLCPCB's assembly stock on 2026-10-18.

| Designators | Value | LCSC | MPN | JLCPCB tier | Stock |
|---|---|---|---|---|---|
| C1,C2,C3 | 22uF | C12891 | CL31A226KAHNNNE | Basic | 490,670 |
| D1 | SS34 | C8678 | SS34 | Basic | 3,870,562 |
| D2 | Green (5V) | C12624 | KT-0603G | Extended | 500,718 |
| J1 | BATT | C173752 | S2B-PH-K-S(LF)(SN) | Extended | 218,971 |
| J2 | OUT | C2691448 | PZ254V-11-04P | Extended | 887,837 |
| L1 | 22uH | C167883 | FNR4030S220MT | Extended | 48,282 |
| R1 | 15k | C22809 | 0603WAF1502T5E | Basic | 4,101,430 |
| R2 | 2k | C22975 | 0603WAF2001T5E | Basic | 11,345,954 |
| R3 | 100k | C25803 | 0603WAF1003T5E | Basic | 19,335,998 |
| R4 | 2.2k | C4190 | 0603WAF2201T5E | Basic | 6,541,694 |
| U1 | MT3608 | C84817 | MT3608 | Extended | 107,165 |

## Ordering

- PCB: upload `fab/power_boost_1s_gerbers.zip`, 2 layers, 28 x 30 mm, 1.6 mm.
- Assembly: `fab/power_boost_1s_bom.csv` and `fab/power_boost_1s_cpl_jlc.csv`, top side.
- The CPL is fitted to each part's own JLCPCB footprint, pad by pad, and re-checked by laying each footprint where its row says: 13 of 13 rows fitted, worst pin-to-pad offset 0.20 mm.

## Notes

- No battery protection on this board: use a cell with its own protection circuit (most JST-lead LiPos have one), or add a protector.
- EN low stops switching but does not disconnect the output: in an asynchronous boost the cell still reaches 5V through the inductor and the SS34, about 0.3-0.4 V below the cell voltage. Put a switch in the cell lead if the load must go fully off.
- JST PH cell leads do not all use the same polarity. Check the lead against the + and - marks before plugging it in.
- Not built or measured: efficiency, ripple and the 1 A figure are unverified.

## How it was made

Designed with the HeyPCB method on KiCad 10, by heypcb-kicad's headless pipeline with Freerouting 2.4.1, from the brief in [`board.json`](board.json).

## Licence

CERN-OHL-S-2.0, © 2026 heypcb.ai. See the collection's LICENSE.

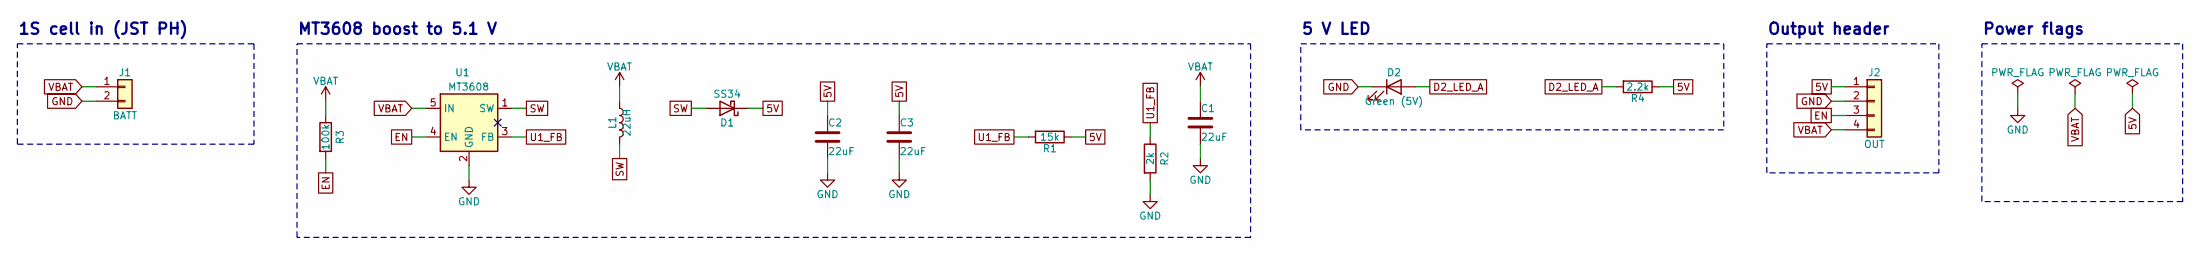
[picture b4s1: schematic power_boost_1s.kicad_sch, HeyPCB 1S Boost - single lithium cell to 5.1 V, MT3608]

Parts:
C1, C2, C3: 22uF; C_1206_3216Metric; MPN CL31A226KAHNNNE; LCSC C12891
D1: SS34; D_SMA; MPN SS34; LCSC C8678
D2: Green (5V); LED_0603_1608Metric; MPN KT-0603G; LCSC C12624
J1: BATT; JST_PH_S2B-PH-K_1x02_P2.00mm_Horizontal; MPN S2B-PH-K-S(LF)(SN); LCSC C173752
J2: OUT; PinHeader_1x04_P2.54mm_Vertical; MPN PZ254V-11-04P; LCSC C2691448
L1: 22uH; L_Changjiang_FNR4030S; MPN FNR4030S220MT; LCSC C167883
R1: 15k; R_0603_1608Metric; MPN 0603WAF1502T5E; LCSC C22809
R2: 2k; R_0603_1608Metric; MPN 0603WAF2001T5E; LCSC C22975
R3: 100k; R_0603_1608Metric; MPN 0603WAF1003T5E; LCSC C25803
R4: 2.2k; R_0603_1608Metric; MPN 0603WAF2201T5E; LCSC C4190
U1: MT3608; SOT-23-6; MPN MT3608; LCSC C84817

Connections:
5V: C2.1, C3.1, D1.1 (K), J2.1, R1.1, R4.1
D2_LED_A: D2.2 (A), R4.2
EN: J2.3, R3.2, U1.4 (EN)
GND: C1.2, C2.2, C3.2, D2.1 (K), J1.2, J2.2, R2.2, U1.2 (GND)
SW: D1.2 (A), L1.2, U1.1 (SW)
U1_FB: R1.2, R2.1, U1.3 (FB)
VBAT: C1.1, J1.1, J2.4, L1.1, R3.1, U1.5 (IN)

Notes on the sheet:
1S cell in (JST PH)
MT3608 boost to 5.1 V
5 V LED
Output header
Power flags

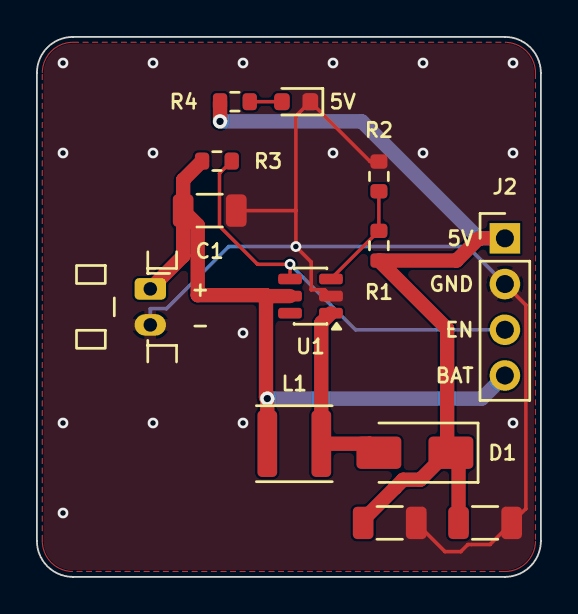
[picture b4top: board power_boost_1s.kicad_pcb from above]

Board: 2 copper layers, 28.0 x 30.0 mm, 13 parts (0 on the bottom side), 7 nets.

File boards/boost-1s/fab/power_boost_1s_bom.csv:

"Reference","Value","Footprint","MPN","LCSC","Qty"
"C1,C2,C3","22uF","Capacitor_SMD:C_1206_3216Metric","CL31A226KAHNNNE","C12891","3"
"D1","SS34","Diode_SMD:D_SMA","SS34","C8678","1"
"D2","Green (5V)","LED_SMD:LED_0603_1608Metric","KT-0603G","C12624","1"
"J1","BATT","Connector_JST:JST_PH_S2B-PH-K_1x02_P2.00mm_Horizontal","S2B-PH-K-S(LF)(SN)","C173752","1"
"J2","OUT","Connector_PinHeader_2.54mm:PinHeader_1x04_P2.54mm_Vertical","PZ254V-11-04P","C2691448","1"
"L1","22uH","Inductor_SMD:L_Changjiang_FNR4030S","FNR4030S220MT","C167883","1"
"R1","15k","Resistor_SMD:R_0603_1608Metric","0603WAF1502T5E","C22809","1"
"R2","2k","Resistor_SMD:R_0603_1608Metric","0603WAF2001T5E","C22975","1"
"R3","100k","Resistor_SMD:R_0603_1608Metric","0603WAF1003T5E","C25803","1"
"R4","2.2k","Resistor_SMD:R_0603_1608Metric","0603WAF2201T5E","C4190","1"
"U1","MT3608","Package_TO_SOT_SMD:SOT-23-6","MT3608","C84817","1"
